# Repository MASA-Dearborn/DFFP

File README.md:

# DFFP
Deployable Fin Flight Package board

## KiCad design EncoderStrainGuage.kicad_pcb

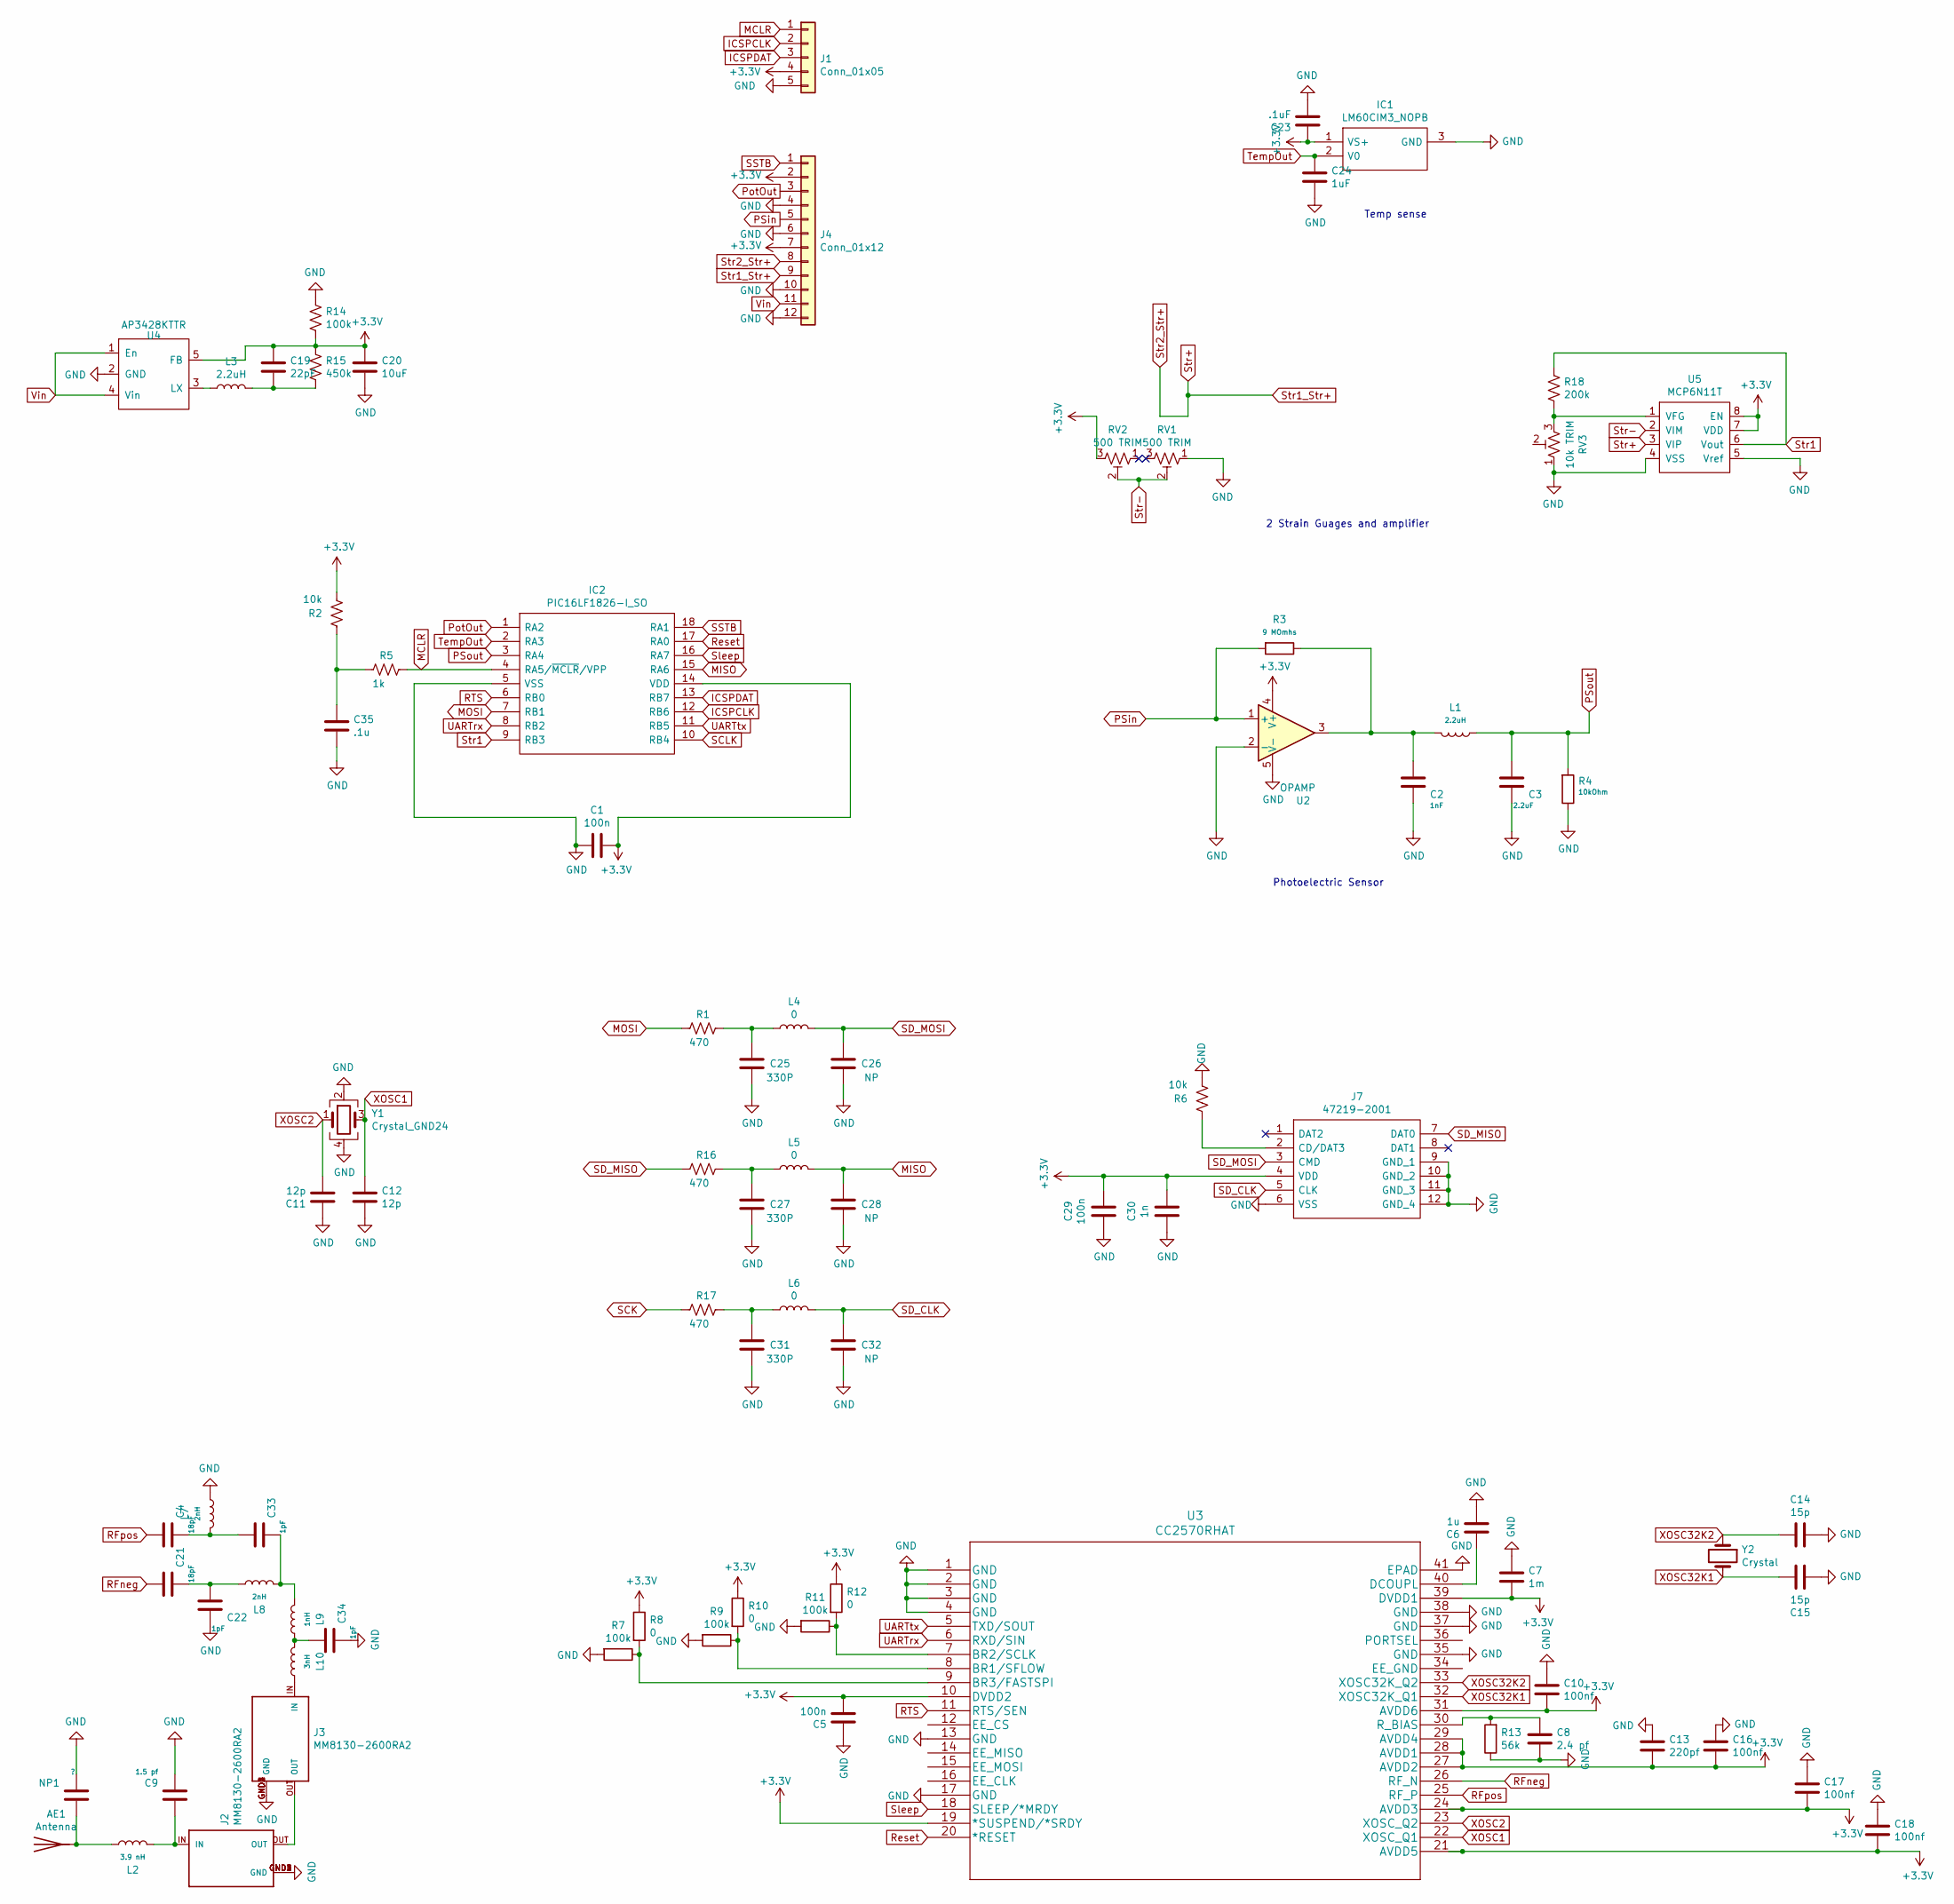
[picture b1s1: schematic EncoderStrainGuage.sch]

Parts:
AE1: Antenna; ANTC3216X140N
C1, C5, C29: 100n; C_0603_1608Metric
C2: 1nF; C_0603_1608Metric
C3: 2.2uF; C_0603_1608Metric
C4, C21: 18pF; C_0402_1005Metric
C6: 1u; C_0603_1608Metric
C7: 1m; C_0603_1608Metric
C8: 2.4 pf; C_0603_1608Metric
C9: 1.5 pf; C_0603_1608Metric
C10, C16, C17, C18: 100nf; C_0603_1608Metric
C11, C12: 12p; C_0603_1608Metric
C13: 220pf; C_0603_1608Metric
C14, C15: 15p; C_0603_1608Metric
C19: 22pF; C_0603_1608Metric
C20: 10uF; C_0603_1608Metric
C22, C33, C34: 1pF; C_0402_1005Metric
C23: .1uF; C_0603_1608Metric
C24: 1uF; C_0603_1608Metric
C25, C27, C31: 330P; C_0603_1608Metric
C26, C28, C32: NP; C_0603_1608Metric
C30: 1n; C_0603_1608Metric
C35: .1u; C_0603_1608Metric
IC1: LM60CIM3_NOPB; SOT95P237X112-3N; Manufacturer_Part_Number LM60CIM3/NOPB; Mouser Part Number 926-LM60CIM3/NOPB
IC2: PIC16LF1826-I_SO; SOIC-18W_7.5x11.6mm_P1.27mm; Mouser Part Number 579-PIC16LF1826-I/SO
J1: Conn_01x05; PinSocket_1x05_P2.54mm_Vertical
J2, J3: MM8130-2600RA2; MURATA_MM8130-2600RA2
J4: Conn_01x12; 1-1734595-2
J7: 47219-2001; SD_472192001; Mouser Part Number 538-47219-2001
L1, L3: 2.2uH; L_0603_1608Metric_Pad1.05x0.95mm_HandSolder
L2: 3.9 nH; L_0603_1608Metric_Pad1.05x0.95mm_HandSolder
L4, L5, L6: 0; L_0603_1608Metric_Pad1.05x0.95mm_HandSolder
L7, L8: 2nH; L_0402_1005Metric
L9: 1nH; L_0402_1005Metric
L10: 3nH; L_0402_1005Metric
NP1: ?; C_0603_1608Metric
R1, R16, R17: 470; R_0603_1608Metric
R2, R6: 10k; R_0603_1608Metric
R3: 9 MOmhs; R_0603_1608Metric
R4: 10kOhm; R_0603_1608Metric
R5: 1k; R_0603_1608Metric
R7, R9, R11, R14: 100k; R_0603_1608Metric
R8, R10, R12: 0; R_0603_1608Metric
R13: 56k; R_0603_1608Metric
R15: 450k; R_0603_1608Metric
R18: 200k; R_0603_1608Metric
RV1, RV2: 500 TRIM; TRIM_3314J-1-202E
RV3: 10k TRIM; TC33X-2_1
U2: OPAMP; SOT95P270X145-5N
U3: CC2570RHAT; QFN40P500X500X90-41N
U4: AP3428KTTR; SOT-23-5
U5: MCP6N11T; MCP6N11T-010E
Y1: Crystal_GND24; FA128
Y2: Crystal; CM7VT1A32768KHZ125PF20PPMTAQC

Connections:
+3V3: C1.1, C5.1, C7.2, C10.2, C13.1, C16.2, C17.2, C18.2, C19.1, C20.1, C23.1, C29.1, C30.1, IC1.1 (VS+), IC2.14 (VDD), J1.4, J4.2, J4.7, J7.4 (VDD), R2.2, R8.1, R10.1, R12.1, R14.2, R15.1, RV2.3, U2.4 (V+), U3.10 (DVDD2), U3.19 (*SUSPEND/*SRDY), U3.21 (AVDD5), U3.24 (AVDD3), U3.27 (AVDD2), U3.28 (AVDD1), U3.29 (AVDD4), U3.31 (AVDD6), U3.39 (DVDD1), U4.5 (FB), U5.7 (VDD), U5.8 (EN)
GND: C1.2, C2.2, C3.2, C5.2, C6.2, C7.1, C8.2, C9.2, C10.1, C11.1, C12.2, C13.2, C14.1, C15.2, C16.1, C17.1, C18.1, C20.2, C22.2, C23.2, C24.2, C25.2, C26.2, C27.2, C28.2, C29.2, C30.2, C31.2, C32.2, C34.2, C35.2, IC1.3 (GND), IC2.5 (VSS), J1.5, J2.GND1 (GND), J2.GND2 (GND), J2.GND3 (GND), J2.GND4 (GND), J3.GND1 (GND), J3.GND2 (GND), J3.GND3 (GND), J3.GND4 (GND), J4.4, J4.6, J4.10, J4.12, J7.6 (VSS), J7.9 (GND_1), J7.10 (GND_2), J7.11 (GND_3), J7.12 (GND_4), L7.1, NP1.2, R4.1, R6.2, R7.2, R9.2, R11.2, R13.1, R14.1, RV1.1, RV3.1, U2.2 (-), U2.5 (V-), U3.1 (GND), U3.2 (GND), U3.3 (GND), U3.4 (GND), U3.13 (GND), U3.17 (GND), U3.35 (GND), U3.37 (GND), U3.38 (GND), U3.41 (EPAD), U4.2 (GND), U5.4 (VSS), U5.5 (Vref), Y1.2, Y1.4
ICSPCLK: IC2.12 (RB6), J1.2
ICSPDAT: IC2.13 (RB7), J1.3
MCLR: IC2.4 (RA5/~MCLR~/VPP), J1.1, R5.1
MISO: C28.1, IC2.15 (RA6), L5.2
MOSI: IC2.7 (RB1), R1.2
unnamed: AE1.1, L2.1, NP1.1
unnamed: C2.1, L1.2, R3.1, U2.3
unnamed: C6.1, U3.40 (DCOUPL)
unnamed: C8.1, R13.2, U3.30 (R_BIAS)
unnamed: C9.1, J2.IN, L2.2
unnamed: C19.2, L3.2, R15.2
unnamed: C21.2, C22.1, L8.1
unnamed: C25.1, L4.1, R1.1
unnamed: C27.1, L5.1, R16.1
unnamed: C31.1, L6.1, R17.1
unnamed: C4.2, C33.1, L7.2
unnamed: C33.2, L8.2, L9.2
unnamed: C34.1, L9.1, L10.2
unnamed: C35.1, R2.1, R5.2
unnamed: J2.OUT, J3.OUT
unnamed: J3.IN, L10.1
unnamed: J7.2 (CD/DAT3), R6.1
unnamed: L3.1, U4.3 (LX)
unnamed: R7.1, R8.2, U3.9 (BR3/FASTSPI)
unnamed: R9.1, R10.2, U3.8 (BR1/SFLOW)
unnamed: R11.1, R12.2, U3.7 (BR2/SCLK)
unnamed: R18.2, RV3.3, U5.1 (VFG)
PSin: J4.5, R3.2, U2.1 (+)
PSout: C3.1, IC2.3 (RA4), L1.1, R4.2
PotOut: IC2.1 (RA2), J4.3
RFneg: C21.1, U3.26 (RF_N)
RFpos: C4.1, U3.25 (RF_P)
RTS: IC2.6 (RB0), U3.11 (RTS/SEN)
Reset: IC2.17 (RA0), U3.20 (*RESET)
SCK: R17.2
SCLK: IC2.10 (RB4)
SD_CLK: C32.1, J7.5 (CLK), L6.2
SD_MISO: J7.7 (DAT0), R16.2
SD_MOSI: C26.1, J7.3 (CMD), L4.2
SSTB: IC2.18 (RA1), J4.1
Sleep: IC2.16 (RA7), U3.18 (SLEEP/*MRDY)
Str1: IC2.9 (RB3), R18.1, U5.6 (Vout)
Str+: J4.8, J4.9, U5.3 (VIP)
Str-: RV1.2, RV2.2, U5.2 (VIM)
TempOut: C24.1, IC1.2 (V0), IC2.2 (RA3)
UARTrx: IC2.8 (RB2), U3.6 (RXD/SIN)
UARTtx: IC2.11 (RB5), U3.5 (TXD/SOUT)
Vin: J4.11, U4.1 (En), U4.4 (Vin)
XOSC1: C12.1, U3.22 (XOSC_Q1), Y1.3
XOSC2: C11.2, U3.23 (XOSC_Q2), Y1.1
XOSC32K1: C15.1, U3.32 (XOSC32K_Q1), Y2.2
XOSC32K2: C14.2, U3.33 (XOSC32K_Q2), Y2.1

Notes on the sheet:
Photoelectric Sensor
2 Strain Guages and amplifier
Temp sense

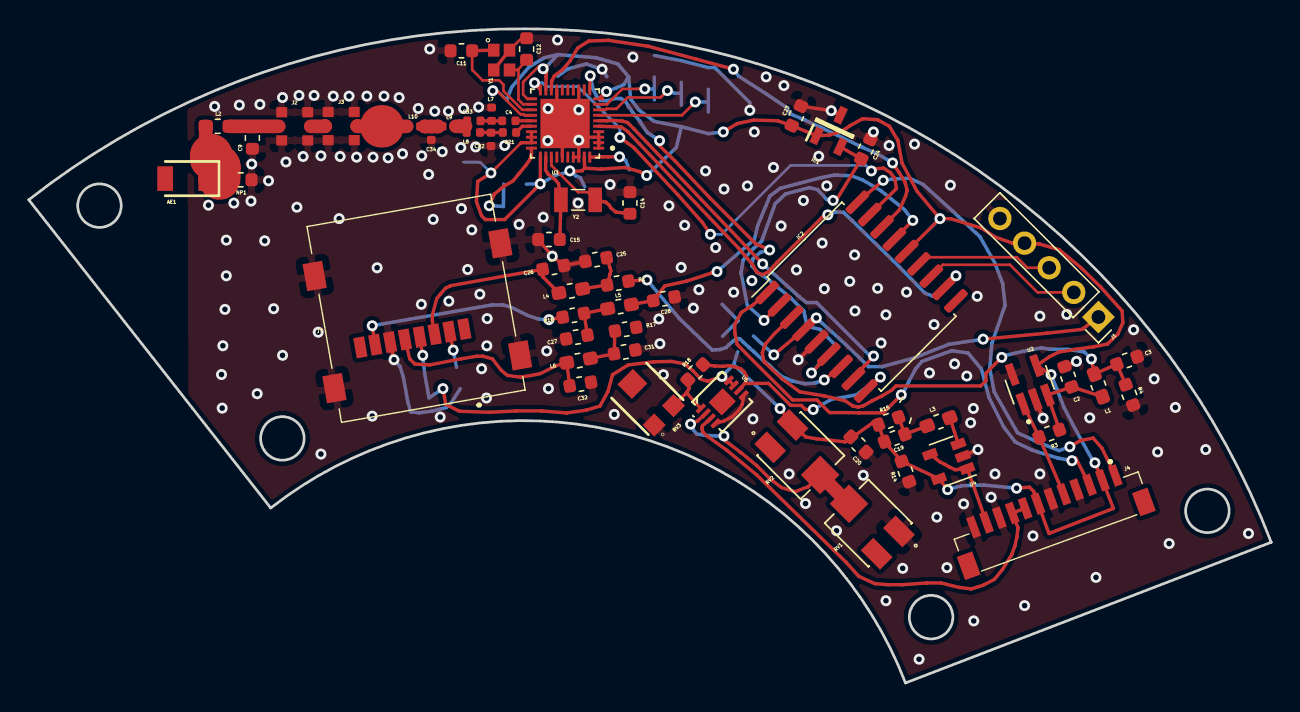
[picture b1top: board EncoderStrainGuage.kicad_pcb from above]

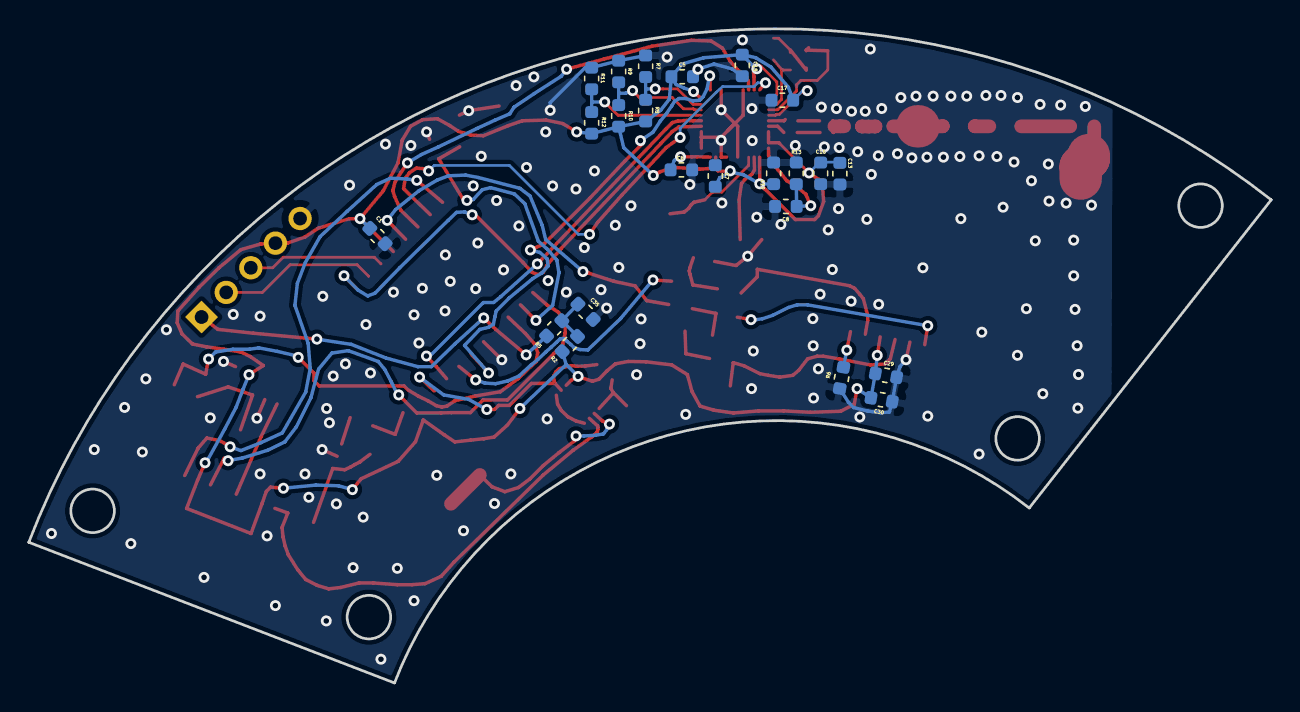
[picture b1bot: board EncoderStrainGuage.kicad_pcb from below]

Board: 2 copper layers, 90.6 x 47.7 mm, 81 parts (23 on the bottom side), 52 nets.

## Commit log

2019-11-20 Initialize
2020-01-09 i am recovering from a crash.
2020-01-16 Updated DFFP
2020-01-16 Add my schematic to the repo
2020-01-17 Strain Guage and Encoder Added.
2020-01-19 finished the ant module of the schematic
2020-01-23 fixed ant module to correct one, fixed wiring to ant module, and added temp sensor
2020-01-23 added str. guage and encoder to PIC
2020-01-23 Gamers added filters
2020-01-24 Fixed everything
2020-01-24 first route on the board
2020-01-24 Fixed RF stuff and improved grounding. Still needs significant review
2020-01-27 Fixed filter
2020-01-30 Wheatstone Bridge added.
2020-01-30 routed the wheatstone bridge to the rest of the board
2020-02-02 Redid the baord onto the correct one
2020-02-06 cleaned up a few routes
2020-02-07 added amplifier IC
2020-02-08 temp sense caps + amplifier IC
2020-02-08 half bridge w/ trimmers and filter on temop sense
2020-02-09 idk what i changed with this one
2020-02-09 SD Card
2020-02-16 "Fixed all routing"
2020-02-16 Fixed a few silk-screens
2020-02-17 Fixed RF stuff
2020-02-17 Fixed trimmer
2020-02-17 Improved RF routing
2020-02-18 Fixed DRC
2020-02-18 Fixed some slightly questionable routing
2020-02-19 fixed silkscreen
